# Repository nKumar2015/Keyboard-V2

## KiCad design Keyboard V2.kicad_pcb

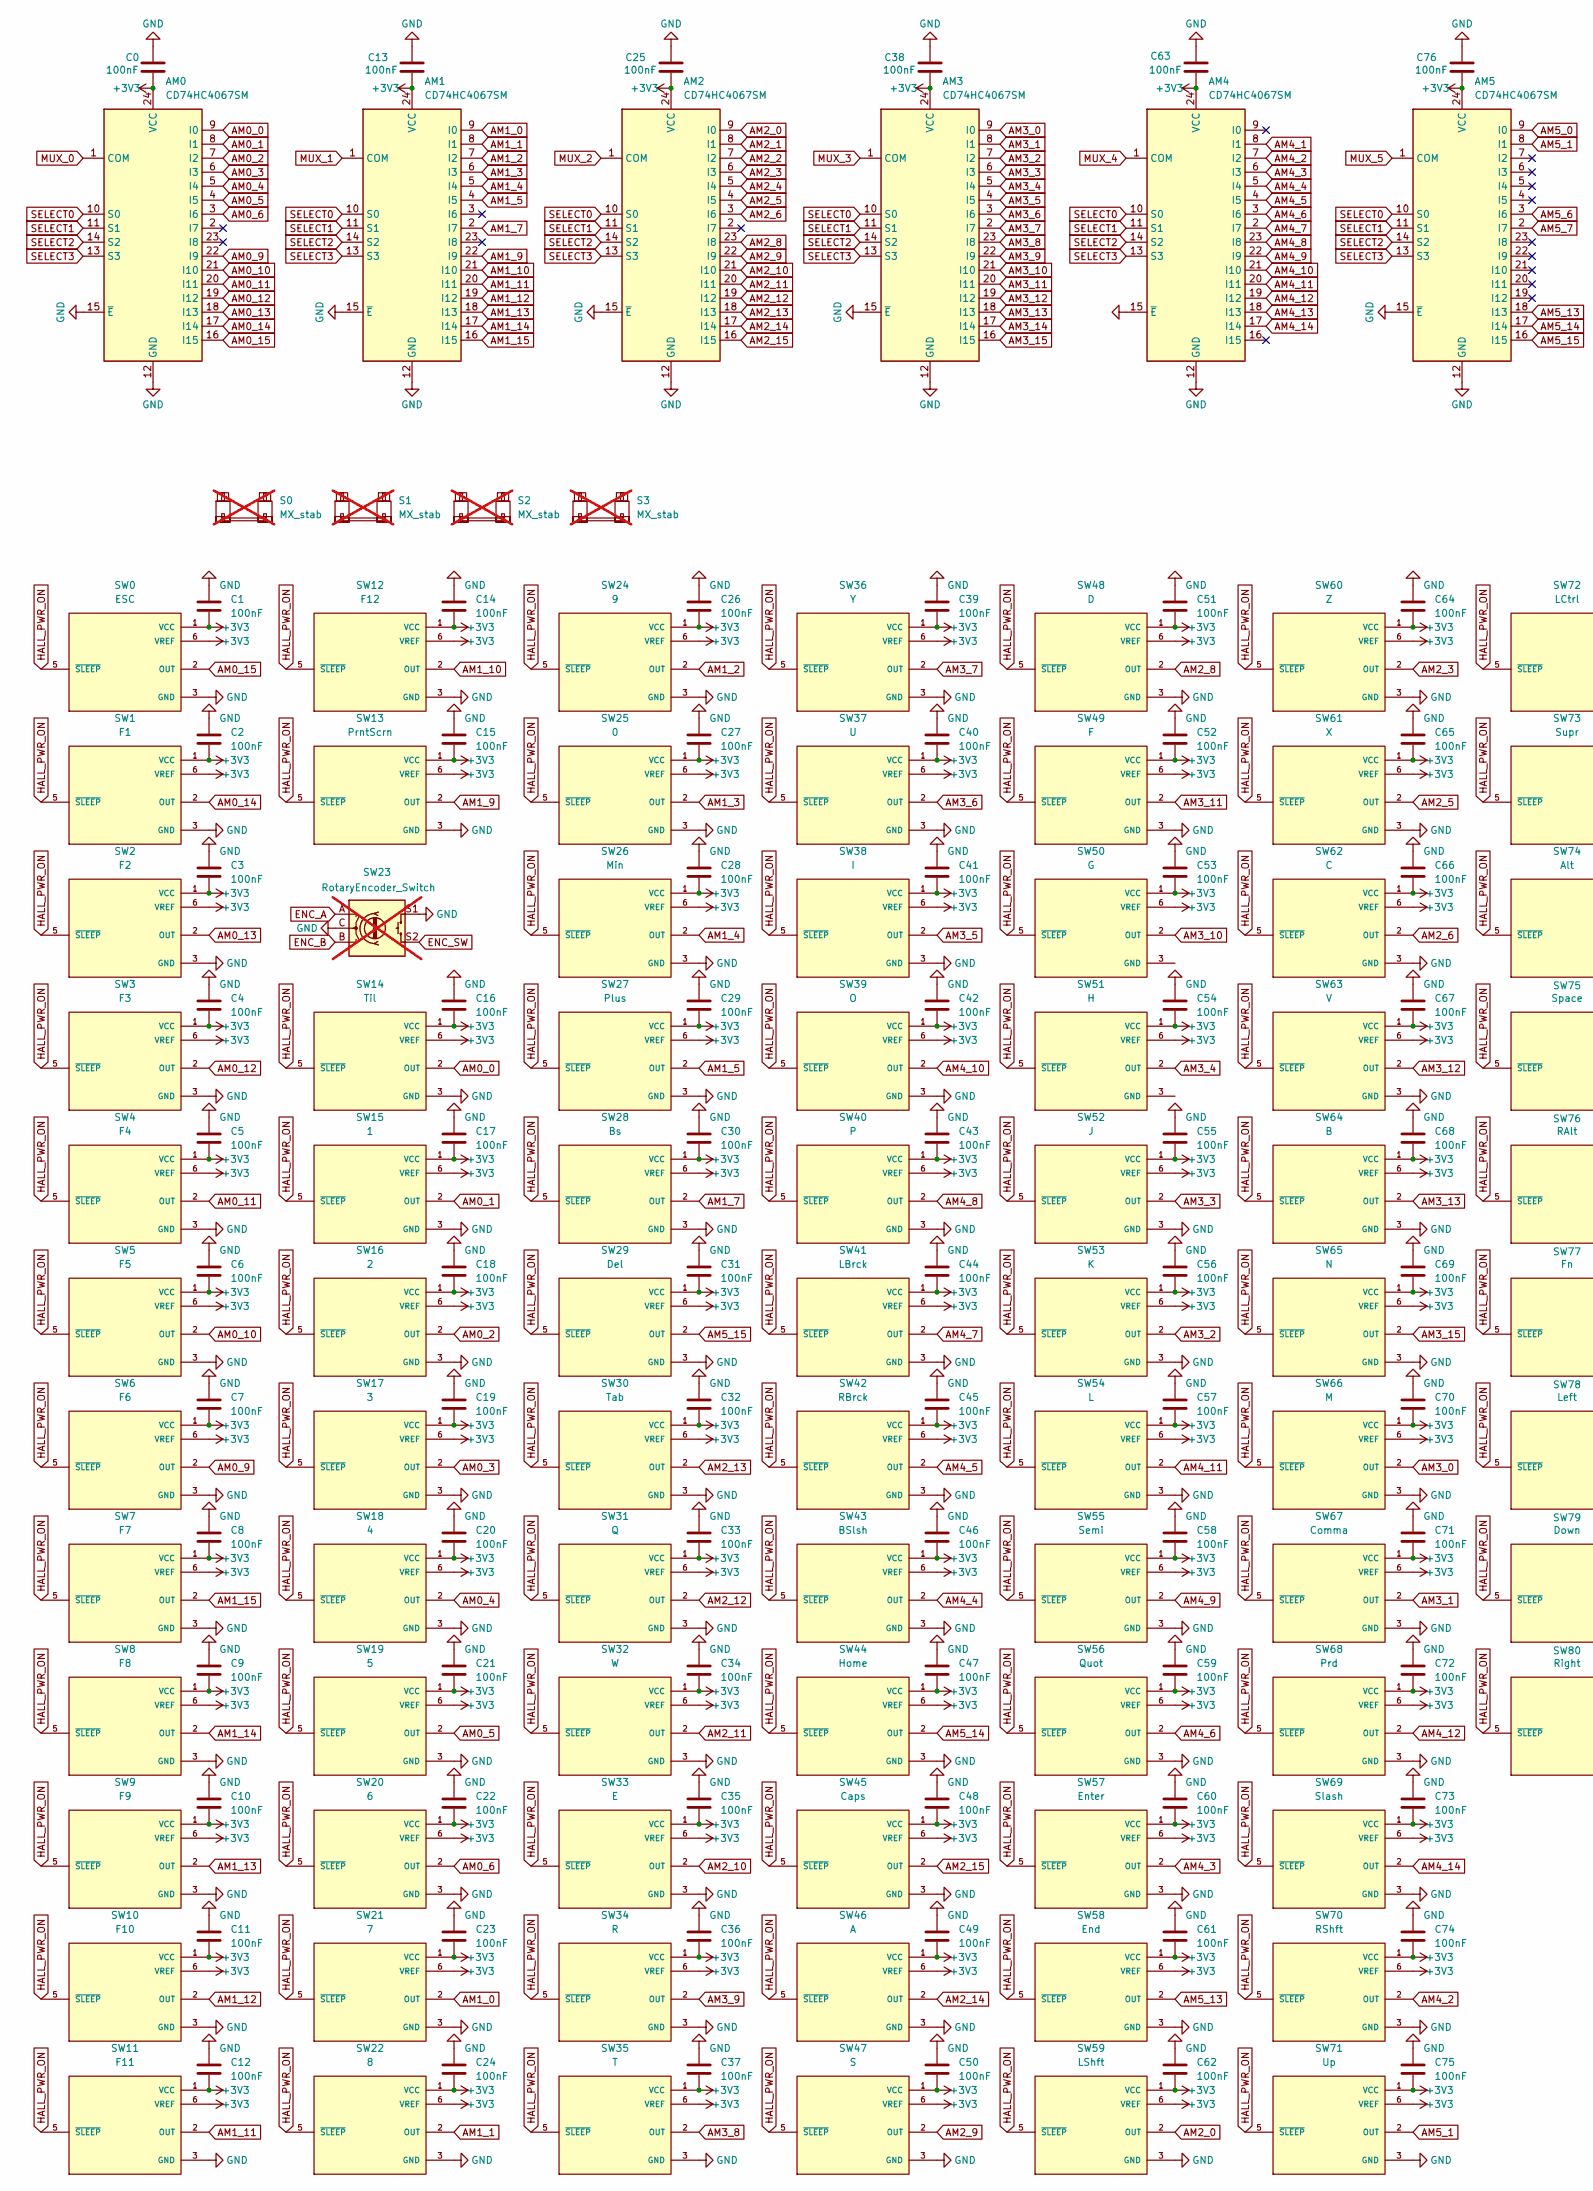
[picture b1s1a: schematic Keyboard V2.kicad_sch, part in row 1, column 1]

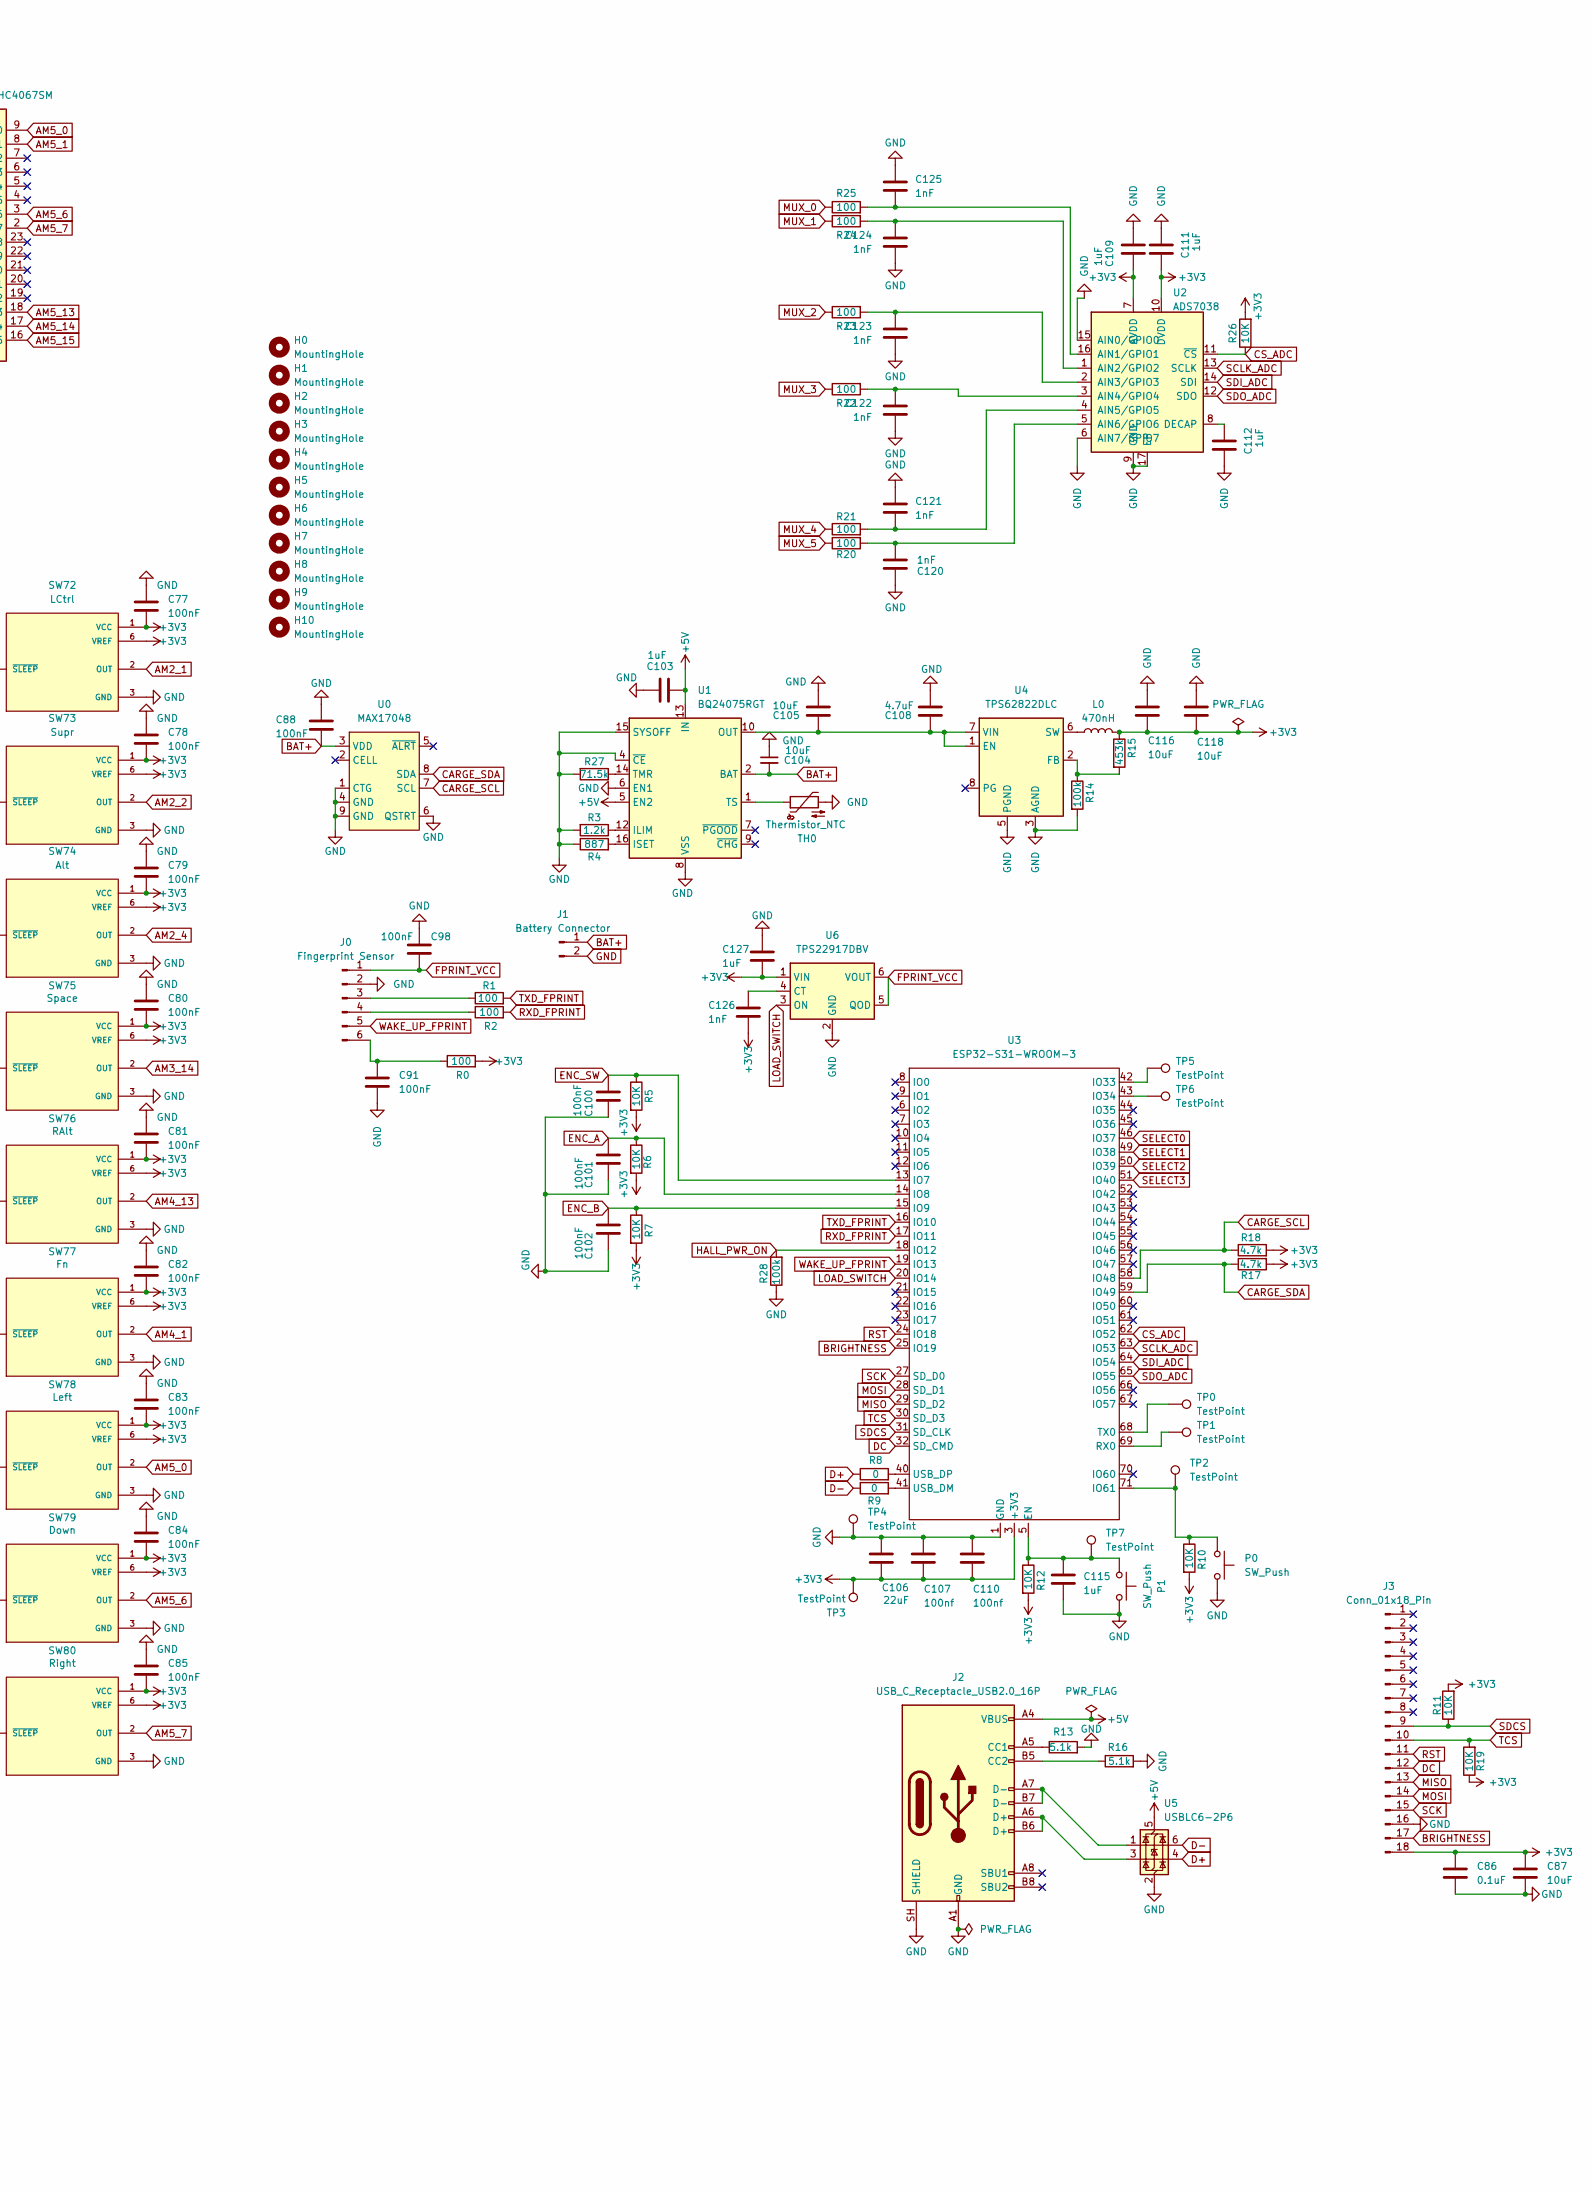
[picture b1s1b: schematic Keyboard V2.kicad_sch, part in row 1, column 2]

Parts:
AM0, AM1, AM2, AM3, AM4, AM5: CD74HC4067SM; SSOP-24_5.3x8.2mm_P0.65mm; LCSC C98457
C0, C13, C25, C38, C63, C76: 100nF; C_0603_1608Metric
C1, C2, C3, C4, C5, C6, C7, C8, C9, C10, C11, C12, C14, C15, C16, C17, C18, C19, C20, C21, C22, C23, C24, C26, C27, C28, C29, C30, C31, C32, C33, C34, C35, C36, C37, C39, C40, C41, C42, C43, C44, C45, C46, C47, C48, C49, C50, C51, C52, C53, C54, C55, C56, C57, C58, C59, C60, C61, C62, C64, C65, C66, C67, C68, C69, C70, C71, C72, C73, C74, C75, C77, C78, C79, C80, C81, C82, C83, C84, C85, C88, C91, C98, C100, C101, C102: 100nF; C_0402_1005Metric
C86: 0.1uF; C_0402_1005Metric
C87, C104, C105, C116, C118: 10uF; C_0603_1608Metric
C103: 1uF; C_0603_1608Metric
C106: 22uF; C_0603_1608Metric
C107, C110: 100nf; C_0402_1005Metric
C108: 4.7uF; C_0603_1608Metric
C109, C111, C112, C115, C127: 1uF; C_0402_1005Metric
C120, C121, C122, C123, C124, C125, C126: 1nF; C_0402_1005Metric
H0, H1, H2, H3, H4, H5, H6, H7, H8, H9, H10: MountingHole; MountingHole_2.2mm_M2
J0: Fingerprint Sensor; JST_BM06B-SRSS-TB_LF__SN_; LCSC C160392
J1: Battery Connector; JST_PH_S2B-PH-K_1x02_P2.00mm_Horizontal; LCSC C295747
J2: USB_C_Receptacle_USB2.0_16P; USB_C_Receptacle_HRO_TYPE-C-31-M-12; LCSC C165948
J3: Conn_01x18_Pin; HRS_FH34SRJ-18S-0.5SH_50_; LCSC C3169386
L0: 470nH; L_0805_2012Metric
P0, P1: SW_Push; SW_SPST_SKQG_WithStem; LCSC C49234130
R0, R1, R2, R20, R21, R22, R23, R24, R25: 100; R_0402_1005Metric
R3: 1.2k; R_0402_1005Metric
R4: 887; R_0402_1005Metric
R5, R6, R7, R10, R12: 10K; R_0603_1608Metric
R8, R9: 0; R_0402_1005Metric
R11, R19, R26: 10K; R_0402_1005Metric
R13, R16: 5.1k; R_0603_1608Metric
R14, R28: 100k; R_0402_1005Metric
R15: 453k; R_0402_1005Metric
R17, R18: 4.7k; R_0402_1005Metric
R27: 71.5k; R_0402_1005Metric
S0: MX_stab; STAB_MX_P_6.25u; not fitted
S1: MX_stab; STAB_MX_2.25u; not fitted
S2: MX_stab; STAB_MX_P_2.25u; not fitted
S3: MX_stab; STAB_MX_P_2u; not fitted
SW0: ESC; SENSOR_A1395SEHLT-T; PARTREV 7; LCSC C146409
SW1: F1; SENSOR_A1395SEHLT-T; PARTREV 7; LCSC C146409
SW2: F2; SENSOR_A1395SEHLT-T; PARTREV 7; LCSC C146409
SW3: F3; SENSOR_A1395SEHLT-T; PARTREV 7; LCSC C146409
SW4: F4; SENSOR_A1395SEHLT-T; PARTREV 7; LCSC C146409
SW5: F5; SENSOR_A1395SEHLT-T; PARTREV 7; LCSC C146409
SW6: F6; SENSOR_A1395SEHLT-T; PARTREV 7; LCSC C146409
SW7: F7; SENSOR_A1395SEHLT-T; PARTREV 7; LCSC C146409
SW8: F8; SENSOR_A1395SEHLT-T; PARTREV 7; LCSC C146409
SW9: F9; SENSOR_A1395SEHLT-T; PARTREV 7; LCSC C146409
SW10: F10; SENSOR_A1395SEHLT-T; PARTREV 7; LCSC C146409
SW11: F11; SENSOR_A1395SEHLT-T; PARTREV 7; LCSC C146409
SW12: F12; SENSOR_A1395SEHLT-T; PARTREV 7; LCSC C146409
SW13: PrntScrn; SENSOR_A1395SEHLT-T; PARTREV 7; LCSC C146409
SW14: Til; SENSOR_A1395SEHLT-T; PARTREV 7; LCSC C146409
SW15: 1; SENSOR_A1395SEHLT-T; PARTREV 7; LCSC C146409
SW16: 2; SENSOR_A1395SEHLT-T; PARTREV 7; LCSC C146409
SW17: 3; SENSOR_A1395SEHLT-T; PARTREV 7; LCSC C146409
SW18: 4; SENSOR_A1395SEHLT-T; PARTREV 7; LCSC C146409
SW19: 5; SENSOR_A1395SEHLT-T; PARTREV 7; LCSC C146409
SW20: 6; SENSOR_A1395SEHLT-T; PARTREV 7; LCSC C146409
SW21: 7; SENSOR_A1395SEHLT-T; PARTREV 7; LCSC C146409
SW22: 8; SENSOR_A1395SEHLT-T; PARTREV 7; LCSC C146409
SW23: RotaryEncoder_Switch; ROT_Alps_EC11E-Switch; not fitted
SW24: 9; SENSOR_A1395SEHLT-T; PARTREV 7; LCSC C146409
SW25: 0; SENSOR_A1395SEHLT-T; PARTREV 7; LCSC C146409
SW26: Min; SENSOR_A1395SEHLT-T; PARTREV 7; LCSC C146409
SW27: Plus; SENSOR_A1395SEHLT-T; PARTREV 7; LCSC C146409
SW28: Bs; SENSOR_A1395SEHLT-T; PARTREV 7; LCSC C146409
SW29: Del; SENSOR_A1395SEHLT-T; PARTREV 7; LCSC C146409
SW30: Tab; SENSOR_A1395SEHLT-T; PARTREV 7; LCSC C146409
SW31: Q; SENSOR_A1395SEHLT-T; PARTREV 7; LCSC C146409
SW32: W; SENSOR_A1395SEHLT-T; PARTREV 7; LCSC C146409
SW33: E; SENSOR_A1395SEHLT-T; PARTREV 7; LCSC C146409
SW34: R; SENSOR_A1395SEHLT-T; PARTREV 7; LCSC C146409
SW35: T; SENSOR_A1395SEHLT-T; PARTREV 7; LCSC C146409
SW36: Y; SENSOR_A1395SEHLT-T; PARTREV 7; LCSC C146409
SW37: U; SENSOR_A1395SEHLT-T; PARTREV 7; LCSC C146409
SW38: I; SENSOR_A1395SEHLT-T; PARTREV 7; LCSC C146409
SW39: O; SENSOR_A1395SEHLT-T; PARTREV 7; LCSC C146409
SW40: P; SENSOR_A1395SEHLT-T; PARTREV 7; LCSC C146409
SW41: LBrck; SENSOR_A1395SEHLT-T; PARTREV 7; LCSC C146409
SW42: RBrck; SENSOR_A1395SEHLT-T; PARTREV 7; LCSC C146409
SW43: BSlsh; SENSOR_A1395SEHLT-T; PARTREV 7; LCSC C146409
SW44: Home; SENSOR_A1395SEHLT-T; PARTREV 7; LCSC C146409
SW45: Caps; SENSOR_A1395SEHLT-T; PARTREV 7; LCSC C146409
SW46: A; SENSOR_A1395SEHLT-T; PARTREV 7; LCSC C146409
SW47: S; SENSOR_A1395SEHLT-T; PARTREV 7; LCSC C146409
SW48: D; SENSOR_A1395SEHLT-T; PARTREV 7; LCSC C146409
SW49: F; SENSOR_A1395SEHLT-T; PARTREV 7; LCSC C146409
SW50: G; SENSOR_A1395SEHLT-T; PARTREV 7; LCSC C146409
SW51: H; SENSOR_A1395SEHLT-T; PARTREV 7; LCSC C146409
SW52: J; SENSOR_A1395SEHLT-T; PARTREV 7; LCSC C146409
SW53: K; SENSOR_A1395SEHLT-T; PARTREV 7; LCSC C146409
SW54: L; SENSOR_A1395SEHLT-T; PARTREV 7; LCSC C146409
SW55: Semi; SENSOR_A1395SEHLT-T; PARTREV 7; LCSC C146409
SW56: Quot; SENSOR_A1395SEHLT-T; PARTREV 7; LCSC C146409
SW57: Enter; SENSOR_A1395SEHLT-T; PARTREV 7; LCSC C146409
SW58: End; SENSOR_A1395SEHLT-T; PARTREV 7; LCSC C146409
SW59: LShft; SENSOR_A1395SEHLT-T; PARTREV 7; LCSC C146409
SW60: Z; SENSOR_A1395SEHLT-T; PARTREV 7; LCSC C146409
SW61: X; SENSOR_A1395SEHLT-T; PARTREV 7; LCSC C146409
SW62: C; SENSOR_A1395SEHLT-T; PARTREV 7; LCSC C146409
SW63: V; SENSOR_A1395SEHLT-T; PARTREV 7; LCSC C146409
SW64: B; SENSOR_A1395SEHLT-T; PARTREV 7; LCSC C146409
SW65: N; SENSOR_A1395SEHLT-T; PARTREV 7; LCSC C146409
SW66: M; SENSOR_A1395SEHLT-T; PARTREV 7; LCSC C146409
SW67: Comma; SENSOR_A1395SEHLT-T; PARTREV 7; LCSC C146409
SW68: Prd; SENSOR_A1395SEHLT-T; PARTREV 7; LCSC C146409
SW69: Slash; SENSOR_A1395SEHLT-T; PARTREV 7; LCSC C146409
SW70: RShft; SENSOR_A1395SEHLT-T; PARTREV 7; LCSC C146409
SW71: Up; SENSOR_A1395SEHLT-T; PARTREV 7; LCSC C146409
SW72: LCtrl; SENSOR_A1395SEHLT-T; PARTREV 7; LCSC C146409
SW73: Supr; SENSOR_A1395SEHLT-T; PARTREV 7; LCSC C146409
SW74: Alt; SENSOR_A1395SEHLT-T; PARTREV 7; LCSC C146409
SW75: Space; SENSOR_A1395SEHLT-T; PARTREV 7; LCSC C146409
SW76: RAlt; SENSOR_A1395SEHLT-T; PARTREV 7; LCSC C146409
SW77: Fn; SENSOR_A1395SEHLT-T; PARTREV 7; LCSC C146409
SW78: Left; SENSOR_A1395SEHLT-T; PARTREV 7; LCSC C146409
SW79: Down; SENSOR_A1395SEHLT-T; PARTREV 7; LCSC C146409
SW80: Right; SENSOR_A1395SEHLT-T; PARTREV 7; LCSC C146409
TH0: Thermistor_NTC; JST_SH_SM02B-SRSS-TB_1x02-1MP_P1.00mm_Horizontal; LCSC C160402
TP0, TP1, TP2, TP5, TP6, TP7: TestPoint; TestPoint_Pad_D1.0mm
TP3, TP4: TestPoint; TestPoint_Pad_D1.5mm
U0: MAX17048; 21-0168_T822&plus_3_MXM
U1: BQ24075RGT; VQFN-16-1EP_3x3mm_P0.5mm_EP1.6x1.6mm
U2: ADS7038; WQFN-16-1EP_3x3mm_P0.5mm_EP1.68x1.68mm_TI_RTE; MPN ADS7038QRTERQ1; LCSC C2876384
U3: ESP32-S31-WROOM-3; LCSC C55371223
U4: TPS62822DLC; Texas_VSON-HR-8_1.5x2mm_P0.5mm
U5: USBLC6-2P6; SOT-666
U6: TPS22917DBV; SOT-23-6; LCSC C2681320

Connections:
+3V3: AM0.24 (VCC), AM1.24 (VCC), AM2.24 (VCC), AM3.24 (VCC), AM4.24 (VCC), AM5.24 (VCC), C0.2, C1.2, C2.2, C3.2, C4.2, C5.2, C6.2, C7.2, C8.2, C9.2, C10.2, C11.2, C12.2, C13.2, C14.2, C15.2, C16.2, C17.2, C18.2, C19.2, C20.2, C21.2, C22.2, C23.2, C24.2, C25.2, C26.2, C27.2, C28.2, C29.2, C30.2, C31.2, C32.2, C33.2, C34.2, C35.2, C36.2, C37.2, C38.2, C39.2, C40.2, C41.2, C42.2, C43.2, C44.2, C45.2, C46.2, C47.2, C48.2, C49.2, C50.2, C51.2, C52.2, C53.2, C54.2, C55.2, C56.2, C57.2, C58.2, C59.2, C60.2, C61.2, C62.2, C63.2, C64.2, C65.2, C66.2, C67.2, C68.2, C69.2, C70.2, C71.2, C72.2, C73.2, C74.2, C75.2, C76.2, C77.2, C78.2, C79.2, C80.2, C81.2, C82.2, C83.2, C84.2, C85.2, C86.1, C87.1, C106.2, C107.2, C109.1, C110.2, C111.2, C116.2, C118.2, C126.2, C127.2, J3.18, L0.2, R0.2, R5.2, R6.2, R7.2, R10.2, R11.2, R12.2, R15.1, R17.2, R18.2, R19.1, R26.2, SW0.1 (VCC), SW0.6 (VREF), SW1.1 (VCC), SW1.6 (VREF), SW2.1 (VCC), SW2.6 (VREF), SW3.1 (VCC), SW3.6 (VREF), SW4.1 (VCC), SW4.6 (VREF), SW5.1 (VCC), SW5.6 (VREF), SW6.1 (VCC), SW6.6 (VREF), SW7.1 (VCC), SW7.6 (VREF), SW8.1 (VCC), SW8.6 (VREF), SW9.1 (VCC), SW9.6 (VREF), SW10.1 (VCC), SW10.6 (VREF), SW11.1 (VCC), SW11.6 (VREF), SW12.1 (VCC), SW12.6 (VREF), SW13.1 (VCC), SW13.6 (VREF), SW14.1 (VCC), SW14.6 (VREF), SW15.1 (VCC), SW15.6 (VREF), SW16.1 (VCC), SW16.6 (VREF), SW17.1 (VCC), SW17.6 (VREF), SW18.1 (VCC), SW18.6 (VREF), SW19.1 (VCC), SW19.6 (VREF), SW20.1 (VCC), SW20.6 (VREF), SW21.1 (VCC), SW21.6 (VREF), SW22.1 (VCC), SW22.6 (VREF), SW24.1 (VCC), SW24.6 (VREF), SW25.1 (VCC), SW25.6 (VREF), SW26.1 (VCC), SW26.6 (VREF), SW27.1 (VCC), SW27.6 (VREF), SW28.1 (VCC), SW28.6 (VREF), SW29.1 (VCC), SW29.6 (VREF), SW30.1 (VCC), SW30.6 (VREF), SW31.1 (VCC), SW31.6 (VREF), SW32.1 (VCC), SW32.6 (VREF), SW33.1 (VCC), SW33.6 (VREF), SW34.1 (VCC), SW34.6 (VREF), SW35.1 (VCC), SW35.6 (VREF), SW36.1 (VCC), SW36.6 (VREF), SW37.1 (VCC), SW37.6 (VREF), SW38.1 (VCC), SW38.6 (VREF), SW39.1 (VCC), SW39.6 (VREF), SW40.1 (VCC), SW40.6 (VREF), SW41.1 (VCC), SW41.6 (VREF), SW42.1 (VCC), SW42.6 (VREF), SW43.1 (VCC), SW43.6 (VREF), SW44.1 (VCC), SW44.6 (VREF), SW45.1 (VCC), SW45.6 (VREF), SW46.1 (VCC), SW46.6 (VREF), SW47.1 (VCC), SW47.6 (VREF), SW48.1 (VCC), SW48.6 (VREF), SW49.1 (VCC), SW49.6 (VREF), SW50.1 (VCC), SW50.6 (VREF), SW51.1 (VCC), SW51.6 (VREF), SW52.1 (VCC), SW52.6 (VREF), SW53.1 (VCC), SW53.6 (VREF), SW54.1 (VCC), SW54.6 (VREF), SW55.1 (VCC), SW55.6 (VREF), SW56.1 (VCC), SW56.6 (VREF), SW57.1 (VCC), SW57.6 (VREF), SW58.1 (VCC), SW58.6 (VREF), SW59.1 (VCC), SW59.6 (VREF), SW60.1 (VCC), SW60.6 (VREF), SW61.1 (VCC), SW61.6 (VREF), SW62.1 (VCC), SW62.6 (VREF), SW63.1 (VCC), SW63.6 (VREF), SW64.1 (VCC), SW64.6 (VREF), SW65.1 (VCC), SW65.6 (VREF), SW66.1 (VCC), SW66.6 (VREF), SW67.1 (VCC), SW67.6 (VREF), SW68.1 (VCC), SW68.6 (VREF), SW69.1 (VCC), SW69.6 (VREF), SW70.1 (VCC), SW70.6 (VREF), SW71.1 (VCC), SW71.6 (VREF), SW72.1 (VCC), SW72.6 (VREF), SW73.1 (VCC), SW73.6 (VREF), SW74.1 (VCC), SW74.6 (VREF), SW75.1 (VCC), SW75.6 (VREF), SW76.1 (VCC), SW76.6 (VREF), SW77.1 (VCC), SW77.6 (VREF), SW78.1 (VCC), SW78.6 (VREF), SW79.1 (VCC), SW79.6 (VREF), SW80.1 (VCC), SW80.6 (VREF), TP3.1 (1_1), U2.7 (AVDD), U2.10 (DVDD), U3.3 (+3V3), U3.4 (+3V3), U6.1 (VIN)
+5V: C103.2, J2.A4 (VBUS), J2.A9 (VBUS), J2.B4 (VBUS), J2.B9 (VBUS), U1.5 (EN2), U1.13 (IN), U5.5 (VBUS)
AM0_0: AM0.9 (I0), SW14.2 (OUT)
AM0_1: AM0.8 (I1), SW15.2 (OUT)
AM0_2: AM0.7 (I2), SW16.2 (OUT)
AM0_3: AM0.6 (I3), SW17.2 (OUT)
AM0_4: AM0.5 (I4), SW18.2 (OUT)
AM0_5: AM0.4 (I5), SW19.2 (OUT)
AM0_6: AM0.3 (I6), SW20.2 (OUT)
AM0_9: AM0.22 (I9), SW6.2 (OUT)
AM0_10: AM0.21 (I10), SW5.2 (OUT)
AM0_11: AM0.20 (I11), SW4.2 (OUT)
AM0_12: AM0.19 (I12), SW3.2 (OUT)
AM0_13: AM0.18 (I13), SW2.2 (OUT)
AM0_14: AM0.17 (I14), SW1.2 (OUT)
AM0_15: AM0.16 (I15), SW0.2 (OUT)
AM1_0: AM1.9 (I0), SW21.2 (OUT)
AM1_1: AM1.8 (I1), SW22.2 (OUT)
AM1_2: AM1.7 (I2), SW24.2 (OUT)
AM1_3: AM1.6 (I3), SW25.2 (OUT)
AM1_4: AM1.5 (I4), SW26.2 (OUT)
AM1_5: AM1.4 (I5), SW27.2 (OUT)
AM1_7: AM1.2 (I7), SW28.2 (OUT)
AM1_9: AM1.22 (I9), SW13.2 (OUT)
AM1_10: AM1.21 (I10), SW12.2 (OUT)
AM1_11: AM1.20 (I11), SW11.2 (OUT)
AM1_12: AM1.19 (I12), SW10.2 (OUT)
AM1_13: AM1.18 (I13), SW9.2 (OUT)
AM1_14: AM1.17 (I14), SW8.2 (OUT)
AM1_15: AM1.16 (I15), SW7.2 (OUT)
AM2_0: AM2.9 (I0), SW59.2 (OUT)
AM2_1: AM2.8 (I1), SW72.2 (OUT)
AM2_2: AM2.7 (I2), SW73.2 (OUT)
AM2_3: AM2.6 (I3), SW60.2 (OUT)
AM2_4: AM2.5 (I4), SW74.2 (OUT)
AM2_5: AM2.4 (I5), SW61.2 (OUT)
AM2_6: AM2.3 (I6), SW62.2 (OUT)
AM2_8: AM2.23 (I8), SW48.2 (OUT)
AM2_9: AM2.22 (I9), SW47.2 (OUT)
AM2_10: AM2.21 (I10), SW33.2 (OUT)
AM2_11: AM2.20 (I11), SW32.2 (OUT)
AM2_12: AM2.19 (I12), SW31.2 (OUT)
AM2_13: AM2.18 (I13), SW30.2 (OUT)
AM2_14: AM2.17 (I14), SW46.2 (OUT)
AM2_15: AM2.16 (I15), SW45.2 (OUT)
AM3_0: AM3.9 (I0), SW66.2 (OUT)
AM3_1: AM3.8 (I1), SW67.2 (OUT)
AM3_2: AM3.7 (I2), SW53.2 (OUT)
AM3_3: AM3.6 (I3), SW52.2 (OUT)
AM3_4: AM3.5 (I4), SW51.2 (OUT)
AM3_5: AM3.4 (I5), SW38.2 (OUT)
AM3_6: AM3.3 (I6), SW37.2 (OUT)
AM3_7: AM3.2 (I7), SW36.2 (OUT)
AM3_8: AM3.23 (I8), SW35.2 (OUT)
AM3_9: AM3.22 (I9), SW34.2 (OUT)
AM3_10: AM3.21 (I10), SW50.2 (OUT)
AM3_11: AM3.20 (I11), SW49.2 (OUT)
AM3_12: AM3.19 (I12), SW63.2 (OUT)
AM3_13: AM3.18 (I13), SW64.2 (OUT)
AM3_14: AM3.17 (I14), SW75.2 (OUT)
AM3_15: AM3.16 (I15), SW65.2 (OUT)
AM4_1: AM4.8 (I1), SW77.2 (OUT)
AM4_2: AM4.7 (I2), SW70.2 (OUT)
AM4_3: AM4.6 (I3), SW57.2 (OUT)
AM4_4: AM4.5 (I4), SW43.2 (OUT)
AM4_5: AM4.4 (I5), SW42.2 (OUT)
AM4_6: AM4.3 (I6), SW56.2 (OUT)
AM4_7: AM4.2 (I7), SW41.2 (OUT)
AM4_8: AM4.23 (I8), SW40.2 (OUT)
AM4_9: AM4.22 (I9), SW55.2 (OUT)
AM4_10: AM4.21 (I10), SW39.2 (OUT)
AM4_11: AM4.20 (I11), SW54.2 (OUT)
AM4_12: AM4.19 (I12), SW68.2 (OUT)
AM4_13: AM4.18 (I13), SW76.2 (OUT)
AM4_14: AM4.17 (I14), SW69.2 (OUT)
AM5_0: AM5.9 (I0), SW78.2 (OUT)
AM5_1: AM5.8 (I1), SW71.2 (OUT)
AM5_6: AM5.3 (I6), SW79.2 (OUT)
AM5_7: AM5.2 (I7), SW80.2 (OUT)
AM5_13: AM5.18 (I13), SW58.2 (OUT)
AM5_14: AM5.17 (I14), SW44.2 (OUT)
AM5_15: AM5.16 (I15), SW29.2 (OUT)
BAT+: C88.2, C104.2, J1.1, U0.3 (VDD), U1.2 (BAT), U1.3 (BAT)
BRIGHTNESS: J3.17, U3.25 (IO19)
CARGE_SCL: R18.1, U0.7 (SCL), U3.58 (IO48)
CARGE_SDA: R17.1, U0.8 (SDA), U3.59 (IO49)
CS_ADC: R26.1, U2.11 (~CS), U3.62 (IO52)
D+: R8.1, U5.4 (I/O2)
D-: R9.1, U5.6 (I/O1)
DC: J3.12, U3.32 (SD_CMD)
ENC_A: C101.1, R6.1, SW23.A, U3.14 (IO8)
ENC_B: C102.2, R7.1, SW23.B, U3.15 (IO9)
ENC_SW: C100.2, R5.1, SW23.S2, U3.13 (IO7)
FPRINT_VCC: C98.1, J0.1, U6.5 (QOD), U6.6 (VOUT)
HALL_PWR_ON: R28.2, SW0.5 (~SLEEP), SW1.5 (~SLEEP), SW2.5 (~SLEEP), SW3.5 (~SLEEP), SW4.5 (~SLEEP), SW5.5 (~SLEEP), SW6.5 (~SLEEP), SW7.5 (~SLEEP), SW8.5 (~SLEEP), SW9.5 (~SLEEP), SW10.5 (~SLEEP), SW11.5 (~SLEEP), SW12.5 (~SLEEP), SW13.5 (~SLEEP), SW14.5 (~SLEEP), SW15.5 (~SLEEP), SW16.5 (~SLEEP), SW17.5 (~SLEEP), SW18.5 (~SLEEP), SW19.5 (~SLEEP), SW20.5 (~SLEEP), SW21.5 (~SLEEP), SW22.5 (~SLEEP), SW24.5 (~SLEEP), SW25.5 (~SLEEP), SW26.5 (~SLEEP), SW27.5 (~SLEEP), SW28.5 (~SLEEP), SW29.5 (~SLEEP), SW30.5 (~SLEEP), SW31.5 (~SLEEP), SW32.5 (~SLEEP), SW33.5 (~SLEEP), SW34.5 (~SLEEP), SW35.5 (~SLEEP), SW36.5 (~SLEEP), SW37.5 (~SLEEP), SW38.5 (~SLEEP), SW39.5 (~SLEEP), SW40.5 (~SLEEP), SW41.5 (~SLEEP), SW42.5 (~SLEEP), SW43.5 (~SLEEP), SW44.5 (~SLEEP), SW45.5 (~SLEEP), SW46.5 (~SLEEP), SW47.5 (~SLEEP), SW48.5 (~SLEEP), SW49.5 (~SLEEP), SW50.5 (~SLEEP), SW51.5 (~SLEEP), SW52.5 (~SLEEP), SW53.5 (~SLEEP), SW54.5 (~SLEEP), SW55.5 (~SLEEP), SW56.5 (~SLEEP), SW57.5 (~SLEEP), SW58.5 (~SLEEP), SW59.5 (~SLEEP), SW60.5 (~SLEEP), SW61.5 (~SLEEP), SW62.5 (~SLEEP), SW63.5 (~SLEEP), SW64.5 (~SLEEP), SW65.5 (~SLEEP), SW66.5 (~SLEEP), SW67.5 (~SLEEP), SW68.5 (~SLEEP), SW69.5 (~SLEEP), SW70.5 (~SLEEP), SW71.5 (~SLEEP), SW72.5 (~SLEEP), SW73.5 (~SLEEP), SW74.5 (~SLEEP), SW75.5 (~SLEEP), SW76.5 (~SLEEP), SW77.5 (~SLEEP), SW78.5 (~SLEEP), SW79.5 (~SLEEP), SW80.5 (~SLEEP), U3.18 (IO12)
LOAD_SWITCH: U3.20 (IO14), U6.3 (ON)
MISO: J3.13, U3.29 (SD_D2)
MOSI: J3.14, U3.28 (SD_D1)
MUX_0: AM0.1 (COM), R25.1
MUX_1: AM1.1 (COM), R24.1
MUX_2: AM2.1 (COM), R23.1
MUX_3: AM3.1 (COM), R22.1
MUX_4: AM4.1 (COM), R21.1
MUX_5: AM5.1 (COM), R20.1
unnamed: J0.3, R1.1
unnamed: J0.4, R2.1
unnamed: C91.1, J0.6, R0.1
unnamed: J2.A5 (CC1), R13.1
unnamed: J2.B5 (CC2), R16.1
unnamed: J2.A6 (D+), J2.B6 (D+), U5.3 (I/O2)
unnamed: J2.A7 (D-), J2.B7 (D-), U5.1 (I/O1)
unnamed: R3.1, U1.12 (ILIM)
unnamed: R4.2, U1.16 (ISET)
unnamed: R27.1, U1.14 (TMR)
unnamed: TH0.1, U1.1 (TS)
unnamed: C125.2, R25.2, U2.16 (AIN1/GPIO1)
unnamed: C124.2, R24.2, U2.1 (AIN2/GPIO2)
unnamed: C123.2, R23.2, U2.2 (AIN3/GPIO3)
unnamed: C122.2, R22.2, U2.3 (AIN4/GPIO4)
unnamed: C121.2, R21.2, U2.4 (AIN5/GPIO5)
unnamed: C120.2, R20.2, U2.5 (AIN6/GPIO6)
unnamed: C112.1, U2.8 (DECAP)
unnamed: C115.1, P1.1, R12.1, TP7.1 (1_1), U3.5 (EN)
unnamed: TP5.1 (1_1), U3.42 (IO33)
unnamed: TP6.1 (1_1), U3.43 (IO34)
unnamed: P0.1, R10.1, TP2.1 (1_1), U3.71 (IO61)
unnamed: TP1.1 (1_1), U3.69 (RX0)
unnamed: TP0.1 (1_1), U3.68 (TX0)
unnamed: R9.2, U3.41 (USB_DM)
unnamed: R8.2, U3.40 (USB_DP)
unnamed: C105.2, C108.2, U1.10 (OUT), U1.11 (OUT), U4.1 (EN), U4.7 (VIN)
unnamed: R14.1, R15.2, U4.2 (FB)
unnamed: L0.1, U4.6 (SW)
unnamed: C126.1, U6.4 (CT)
RST: J3.11, U3.24 (IO18)
RXD_FPRINT: R2.2, U3.17 (IO11)
SCK: J3.15, U3.27 (SD_D0)
SCLK_ADC: U2.13 (SCLK), U3.63 (IO53)
SDCS: J3.9, R11.1, U3.31 (SD_CLK)
SDI_ADC: U2.14 (SDI), U3.64 (IO54)
SDO_ADC: U2.12 (SDO), U3.65 (IO55)
SELECT0: AM0.10 (S0), AM1.10 (S0), AM2.10 (S0), AM3.10 (S0), AM4.10 (S0), AM5.10 (S0), U3.46 (IO37)
SELECT1: AM0.11 (S1), AM1.11 (S1), AM2.11 (S1), AM3.11 (S1), AM4.11 (S1), AM5.11 (S1), U3.49 (IO38)
SELECT2: AM0.14 (S2), AM1.14 (S2), AM2.14 (S2), AM3.14 (S2), AM4.14 (S2), AM5.14 (S2), U3.50 (IO39)
SELECT3: AM0.13 (S3), AM1.13 (S3), AM2.13 (S3), AM3.13 (S3), AM4.13 (S3), AM5.13 (S3), U3.51 (IO40)
TCS: J3.10, R19.2, U3.30 (SD_D3)
TXD_FPRINT: R1.2, U3.16 (IO10)
WAKE_UP_FPRINT: J0.5, U3.19 (IO13)

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
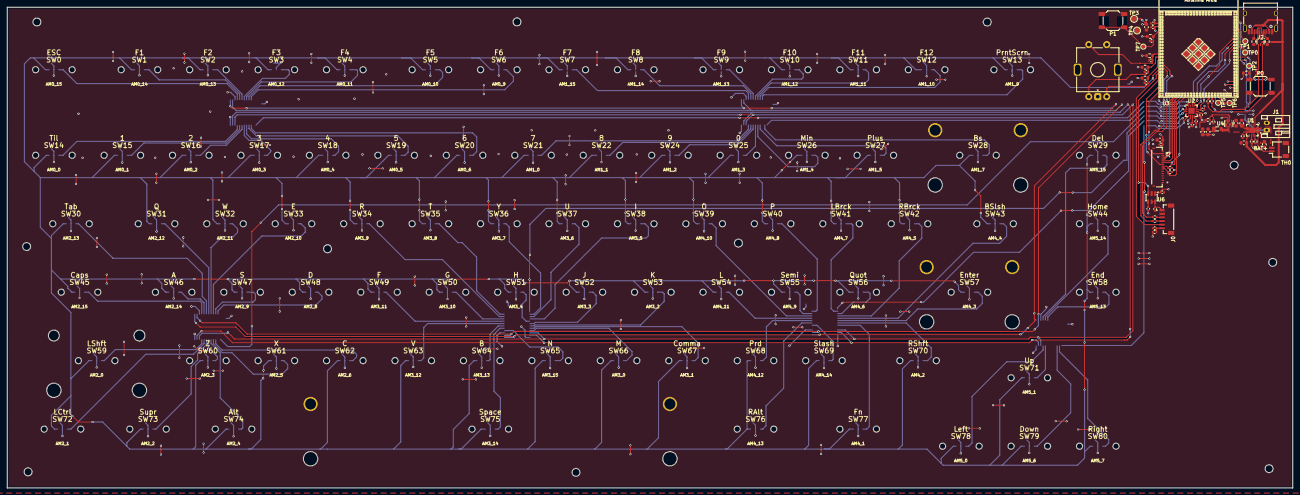
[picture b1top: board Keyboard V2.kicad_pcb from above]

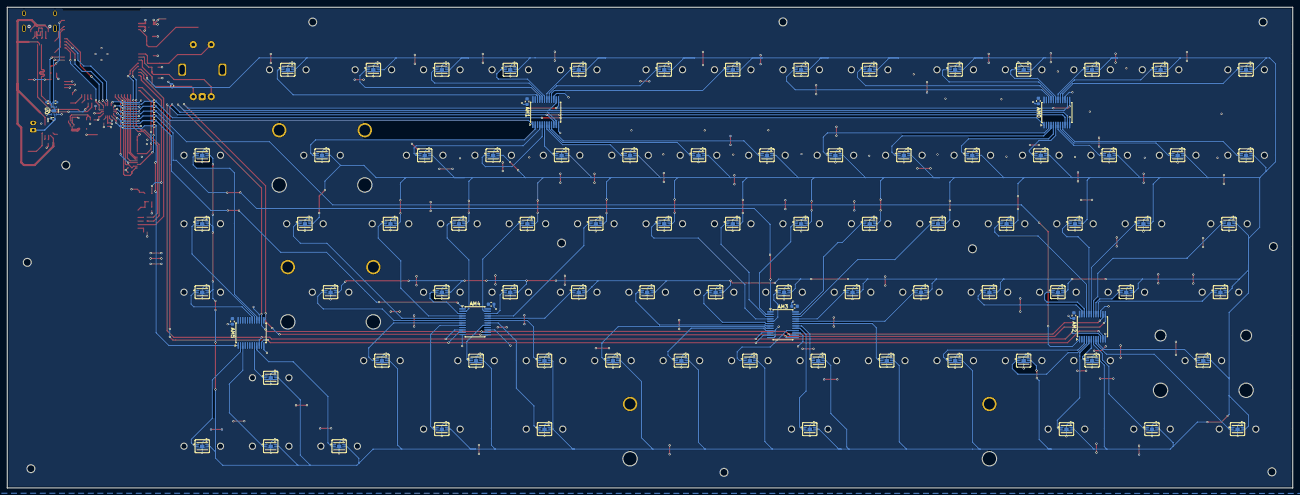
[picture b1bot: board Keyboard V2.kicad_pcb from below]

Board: 4 copper layers, 357.7 x 133.8 mm, 269 parts (189 on the bottom side), 149 nets.

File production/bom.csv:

Designator,Footprint,Quantity,Value,LCSC Part #
"AM0, AM1, AM2, AM3, AM4, AM5",SSOP-24_5.3x8.2mm_P0.65mm,6,CD74HC4067SM,C98457
"C0, C13, C25, C38, C63, C76",0603,6,100nF,
"C1, C10, C100, C101, C102, C107, C11, C110, C12, C14, C15, C16, C17, C18, C19, C2, C20, C21, C22, C23, C24, C26, C27, C28, C29, C3, C30, C31, C32, C33, C34, C35, C36, C37, C39, C4, C40, C41, C42, C43, C44, C45, C46, C47, C48, C49, C5, C50, C51, C52, C53, C54, C55, C56, C57, C58, C59, C6, C60, C61, C62, C64, C65, C66, C67, C68, C69, C7, C70, C71, C72, C73, C74, C75, C77, C78, C79, C8, C80, C81, C82, C83, C84, C85, C88, C9, C91, C98",0402,88,100nF,
C103,0603,1,1uF,
"C104, C105, C116, C118, C87",0603,5,10uF,
C106,0603,1,22uF,
C108,0603,1,4.7uF,
"C109, C111, C112, C115, C127",0402,5,1uF,
"C120, C121, C122, C123, C124, C125, C126",0402,7,1nF,
C86,0402,1,0.1uF,
J0,JST_BM06B-SRSS-TB_LF__SN_,1,Fingerprint Sensor,C160392
J1,JST_PH_S2B-PH-K_1x02_P2.00mm_Horizontal,1,Battery Connector,C295747
J2,USB_C_Receptacle_HRO_TYPE-C-31-M-12,1,USB_C_Receptacle_USB2.0_16P,C165948
J3,HRS_FH34SRJ-18S-0.5SH_50_,1,Conn_01x18_Pin,C3169386
L0,0805,1,470nH,
"P0, P1",SW_SPST_SKQG_WithStem,2,SW_Push,C49234130
"R0, R1, R2, R20, R21, R22, R23, R24, R25",0402,9,100,
"R10, R12, R5, R6, R7",0603,5,10K,
"R11, R19, R26",0402,3,10K,
"R13, R16",0603,2,5.1k,
"R14, R28",0402,2,100k,
R15,0402,1,453k,
"R17, R18",0402,2,4.7k,
R27,0402,1,71.5k,
R3,0402,1,1.2k,
R4,0402,1,887,
"R8, R9",0402,2,0,
SW0,SENSOR_A1395SEHLT-T,1,ESC,C146409
SW1,SENSOR_A1395SEHLT-T,1,F1,C146409
SW10,SENSOR_A1395SEHLT-T,1,F10,C146409
SW11,SENSOR_A1395SEHLT-T,1,F11,C146409
SW12,SENSOR_A1395SEHLT-T,1,F12,C146409
SW13,SENSOR_A1395SEHLT-T,1,PrntScrn,C146409
SW14,SENSOR_A1395SEHLT-T,1,Til,C146409
SW15,SENSOR_A1395SEHLT-T,1,1,C146409
SW16,SENSOR_A1395SEHLT-T,1,2,C146409
SW17,SENSOR_A1395SEHLT-T,1,3,C146409
SW18,SENSOR_A1395SEHLT-T,1,4,C146409
SW19,SENSOR_A1395SEHLT-T,1,5,C146409
SW2,SENSOR_A1395SEHLT-T,1,F2,C146409
SW20,SENSOR_A1395SEHLT-T,1,6,C146409
SW21,SENSOR_A1395SEHLT-T,1,7,C146409
SW22,SENSOR_A1395SEHLT-T,1,8,C146409
SW24,SENSOR_A1395SEHLT-T,1,9,C146409
SW25,SENSOR_A1395SEHLT-T,1,0,C146409
SW26,SENSOR_A1395SEHLT-T,1,Min,C146409
SW27,SENSOR_A1395SEHLT-T,1,Plus,C146409
SW28,SENSOR_A1395SEHLT-T,1,Bs,C146409
SW29,SENSOR_A1395SEHLT-T,1,Del,C146409
SW3,SENSOR_A1395SEHLT-T,1,F3,C146409
SW30,SENSOR_A1395SEHLT-T,1,Tab,C146409
SW31,SENSOR_A1395SEHLT-T,1,Q,C146409
SW32,SENSOR_A1395SEHLT-T,1,W,C146409
SW33,SENSOR_A1395SEHLT-T,1,E,C146409
SW34,SENSOR_A1395SEHLT-T,1,R,C146409
SW35,SENSOR_A1395SEHLT-T,1,T,C146409
SW36,SENSOR_A1395SEHLT-T,1,Y,C146409
SW37,SENSOR_A1395SEHLT-T,1,U,C146409
SW38,SENSOR_A1395SEHLT-T,1,I,C146409
SW39,SENSOR_A1395SEHLT-T,1,O,C146409
SW4,SENSOR_A1395SEHLT-T,1,F4,C146409
SW40,SENSOR_A1395SEHLT-T,1,P,C146409
SW41,SENSOR_A1395SEHLT-T,1,LBrck,C146409
SW42,SENSOR_A1395SEHLT-T,1,RBrck,C146409
SW43,SENSOR_A1395SEHLT-T,1,BSlsh,C146409
SW44,SENSOR_A1395SEHLT-T,1,Home,C146409
SW45,SENSOR_A1395SEHLT-T,1,Caps,C146409
SW46,SENSOR_A1395SEHLT-T,1,A,C146409
SW47,SENSOR_A1395SEHLT-T,1,S,C146409
SW48,SENSOR_A1395SEHLT-T,1,D,C146409
SW49,SENSOR_A1395SEHLT-T,1,F,C146409
SW5,SENSOR_A1395SEHLT-T,1,F5,C146409
SW50,SENSOR_A1395SEHLT-T,1,G,C146409
SW51,SENSOR_A1395SEHLT-T,1,H,C146409
SW52,SENSOR_A1395SEHLT-T,1,J,C146409
SW53,SENSOR_A1395SEHLT-T,1,K,C146409
SW54,SENSOR_A1395SEHLT-T,1,L,C146409
SW55,SENSOR_A1395SEHLT-T,1,Semi,C146409
SW56,SENSOR_A1395SEHLT-T,1,Quot,C146409
SW57,SENSOR_A1395SEHLT-T,1,Enter,C146409
SW58,SENSOR_A1395SEHLT-T,1,End,C146409
SW59,SENSOR_A1395SEHLT-T,1,LShft,C146409
SW6,SENSOR_A1395SEHLT-T,1,F6,C146409
SW60,SENSOR_A1395SEHLT-T,1,Z,C146409
SW61,SENSOR_A1395SEHLT-T,1,X,C146409
SW62,SENSOR_A1395SEHLT-T,1,C,C146409
SW63,SENSOR_A1395SEHLT-T,1,V,C146409
SW64,SENSOR_A1395SEHLT-T,1,B,C146409
SW65,SENSOR_A1395SEHLT-T,1,N,C146409
SW66,SENSOR_A1395SEHLT-T,1,M,C146409
SW67,SENSOR_A1395SEHLT-T,1,Comma,C146409
SW68,SENSOR_A1395SEHLT-T,1,Prd,C146409
SW69,SENSOR_A1395SEHLT-T,1,Slash,C146409
SW7,SENSOR_A1395SEHLT-T,1,F7,C146409
SW70,SENSOR_A1395SEHLT-T,1,RShft,C146409
SW71,SENSOR_A1395SEHLT-T,1,Up,C146409
SW72,SENSOR_A1395SEHLT-T,1,LCtrl,C146409
SW73,SENSOR_A1395SEHLT-T,1,Supr,C146409
SW74,SENSOR_A1395SEHLT-T,1,Alt,C146409
SW75,SENSOR_A1395SEHLT-T,1,Space,C146409
SW76,SENSOR_A1395SEHLT-T,1,RAlt,C146409
SW77,SENSOR_A1395SEHLT-T,1,Fn,C146409
SW78,SENSOR_A1395SEHLT-T,1,Left,C146409
SW79,SENSOR_A1395SEHLT-T,1,Down,C146409
SW8,SENSOR_A1395SEHLT-T,1,F8,C146409
SW80,SENSOR_A1395SEHLT-T,1,Right,C146409
SW9,SENSOR_A1395SEHLT-T,1,F9,C146409
TH0,JST_SH_SM02B-SRSS-TB_1x02-1MP_P1.00mm_Horizontal,1,Thermistor_NTC,C160402
U0,21-0168_T822&plus_3_MXM,1,MAX17048,
U1,VQFN-16-1EP_3x3mm_P0.5mm_EP1.6x1.6mm,1,BQ24075RGT,
U2,WQFN-16-1EP_3x3mm_P0.5mm_EP1.68x1.68mm_TI_RTE,1,ADS7038,C2876384
U3,ESP32-S31-WROOM-3,1,ESP32-S31-WROOM-3,C55371223
U4,Texas_VSON-HR-8_1.5x2mm_P0.5mm,1,TPS62822DLC,
U5,SOT-666,1,USBLC6-2P6,
U6,SOT-23-6,1,TPS22917DBV,C2681320
